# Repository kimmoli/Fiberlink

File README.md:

Fiberlink
=========

USB <-> 1000µm Fiber <-> RS-232 <-> RS-485

USB <-> RS232
SJ6, SJ7

USB <-> RS485
SJ10, SJ11, SJ15

USB <-> FIBER
SJ3, SJ5

RS232 <-> RS485
SJ12, SJ13, SJ14

RS232 <-> FIBER
SJ2, SJ4

FIBER <-> RS485
SJ8, SJ9, SJ14

SJ2 FIBER RX TO RS232
SJ3 FIBER RX TO USB
SJ4 RS232 RX TO FIBER
SJ5 USB RX TO FIBER
SJ6 USB RX TO RS232
SJ7 RS232 RX TO USB
SJ8 RS485 RX TO FIBER
SJ9 FIBER RX TO RS485
SJ10 RS485 RX TO USB
SJ11 USB RX TO RS485
SJ12 RS232 RX TO RS485
SJ13 RS485 RX TO RS232
SJ14 CARRIER SENSE TO RX485 TXEN
SJ15 USB TXEN TO RS485 TXEN

SJ17 FTDI POWER SELECT

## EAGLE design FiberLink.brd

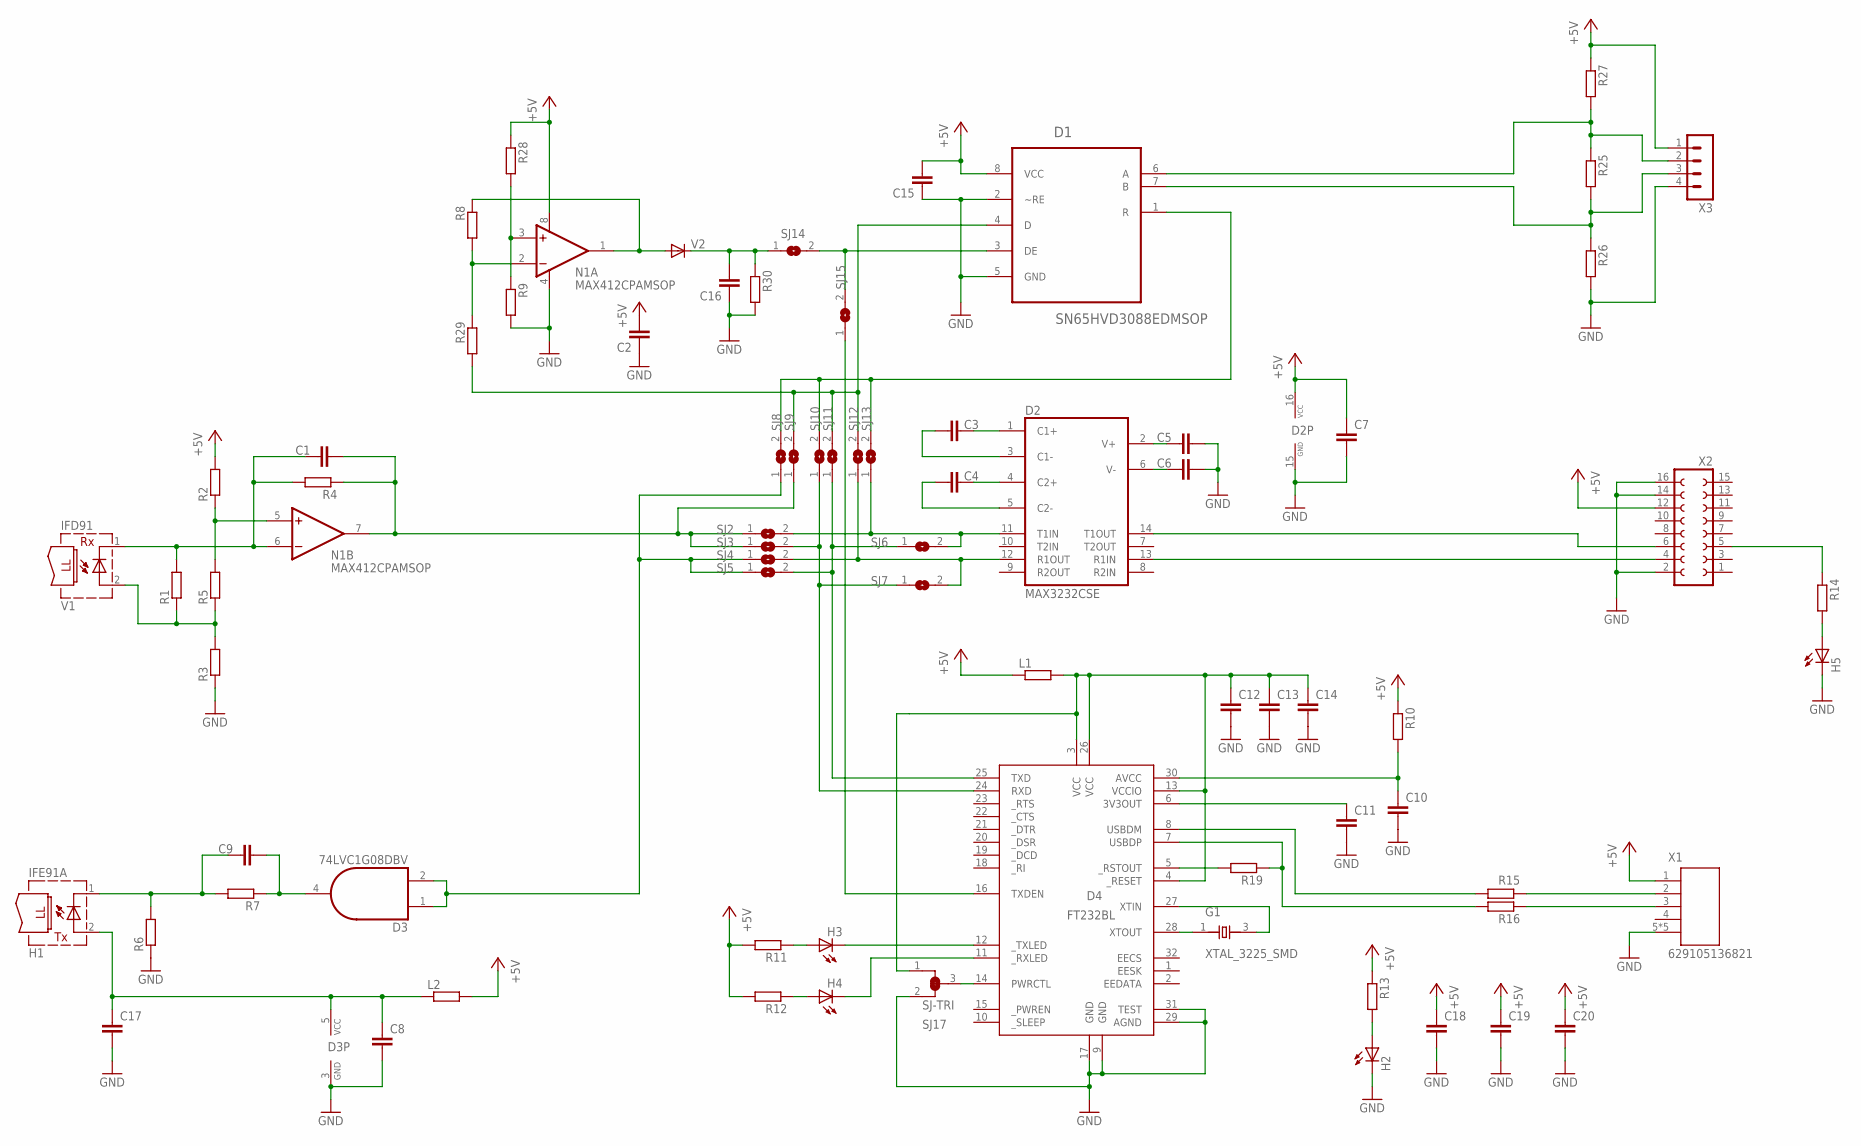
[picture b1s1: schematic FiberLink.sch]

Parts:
C1, C2, C3, C4, C5, C6, C7, C8, C9, C10, C11, C12, C13, C14, C15, C16, C17: C-EUC0402; C0402
C18, C19, C20: C-EUC0805; C0805
D1: SN65HVD3088EDMSOP; SOP65P490X110-8N
D2: MAX3232CSE; SO16
D3: 74LVC1G08DBV; SOT23-5
D4: FT232BL; LQFP32
G1: XTAL_3225_SMD; X_3225
H1: IFE91A; IFO-IFX
H2, H3, H4, H5: LEDCHIP-LED0603; CHIP-LED0603
L1, L2: R-EU_R0402; R0402_VISHAY
N1: MAX412CPAMSOP; SOP65P490X110-8N
R1, R2, R3, R4, R5, R8, R9, R10, R11, R12, R13, R14, R15, R16, R19, R28, R29, R30: R-EU_R0402; R0402_VISHAY
R6, R7, R25: R-EU_R1206; R1206
R26, R27: R-EU_R0603; R0603
SJ2, SJ3, SJ4, SJ5, SJ6, SJ7, SJ8, SJ9, SJ10, SJ11, SJ12, SJ13, SJ14, SJ15: SJ; SJ-SMALL
SJ17: SJ-TRI; SJ-SMALL-TRI
V1: IFD91; IFO-IFX
V2: DIODE-SOD323-R; SOD323-R
X1: 629105136821
X2: FE08-2
X3: MA04-1

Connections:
485_HIGH: D1.6 (A), R25.1, R27.2, X3.2
485_LOW: D1.7 (B), R25.2, R26.1, X3.3
+5V: C2.2, C7.1, C15.2, C18.1, C19.1, C20.1, D1.8 (VCC), D2.16 (VCC), L1.1, L2.2, N1.8 (V+), R2.2, R10.1, R11.2, R12.2, R13.1, R27.1, R28.1, X1.1, X2.12, X3.1
AVCC: C10.1, D4.30 (AVCC), R10.2
CARRIER_SENSE: C16.2, R30.1, SJ14.1, V2.C
FPGADONE: R14.1, X2.5
G1: D4.27 (XTIN), G1.3 (X2)
GND: C2.1, C5.2, C6.2, C7.2, C8.2, C10.2, C11.2, C12.2, C13.2, C14.2, C15.1, C16.1, C17.2, C18.2, C19.2, C20.2, D1.2 (~RE), D1.5 (GND), D2.15 (GND), D3.3 (GND), D4.9 (GND), D4.17 (GND), D4.29 (AGND), D4.31 (TEST), H2.C, H5.C, N1.4 (V-), R3.1, R6.1, R9.2, R26.2, R30.2, SJ17.2, X1.5, X1.Z1 (5), X1.Z2 (5), X1.Z3 (5), X1.Z4 (5), X2.2, X2.14, X2.16, X3.4
unnamed: C1.1, N1.6 (-IN), R1.2, R4.2, V1.1 (C)
unnamed: N1.1 (OUT), R8.1, V2.A
unnamed: R1.1, R3.2, R5.1, V1.2 (A)
unnamed: D4.12 (_TXLED), H3.C
unnamed: N1.5 (+IN), R2.1, R5.2
unnamed: C4.2, D2.5 (C2-)
unnamed: C4.1, D2.4 (C2+)
unnamed: C3.2, D2.3 (C1-)
unnamed: C3.1, D2.1 (C1+)
unnamed: C6.1, D2.6 (V-)
unnamed: C5.1, D2.2 (V+)
unnamed: D2.14 (T1OUT), X2.6
unnamed: D2.13 (R1IN), X2.4
unnamed: D4.11 (_RXLED), H4.C
unnamed: C9.1, H1.1 (C), R6.2, R7.2
unnamed: N1.3 (+IN), R9.1, R28.2
unnamed: C9.2, D3.4 (O), R7.1
unnamed: H3.A, R11.1
unnamed: R15.1, X1.2
unnamed: H4.A, R12.1
unnamed: D4.8 (USBDM), R15.2
unnamed: H2.A, R13.2
unnamed: D4.7 (USBDP), R16.2, R19.1
unnamed: R16.1, X1.3
unnamed: H5.A, R14.2
unnamed: D4.14 (PWRCTL), SJ17.3
unnamed: D4.5 (_RSTOUT), R19.2
unnamed: N1.2 (-IN), R8.2, R29.1
unnamed: D4.28 (XTOUT), G1.1 (X1)
RXD_232: D2.12 (R1OUT), SJ4.2, SJ7.2, SJ12.1
RXD_485: D1.1 (R), SJ8.2, SJ10.2, SJ13.2
RXD_FIBER: C1.2, N1.7 (OUT), R4.1, SJ2.1, SJ3.1, SJ9.1
RXD_USB: D4.24 (RXD), SJ3.2, SJ7.1, SJ10.1
TXD_232: D2.11 (T1IN), SJ2.2, SJ6.2, SJ13.1
TXD_485: D1.4 (D), R29.2, SJ9.2, SJ11.2, SJ12.2
TXD_FIBER: D3.1 (I0), D3.2 (I1), SJ4.1, SJ5.1, SJ8.1
TXD_USB: D4.25 (TXD), SJ5.2, SJ6.1, SJ11.1
TXEN_485: D1.3 (DE), SJ14.2, SJ15.2
TXEN_USB: D4.16 (TXDEN), SJ15.1
TX_VCC: C8.1, C17.1, D3.5 (VCC), H1.2 (A), L2.1
USB3V3: C11.1, D4.6 (3V3OUT)
USBVCC: C12.1, C13.1, C14.1, D4.3 (VCC), D4.4 (_RESET), D4.13 (VCCIO), D4.26 (VCC), L1.2, SJ17.1

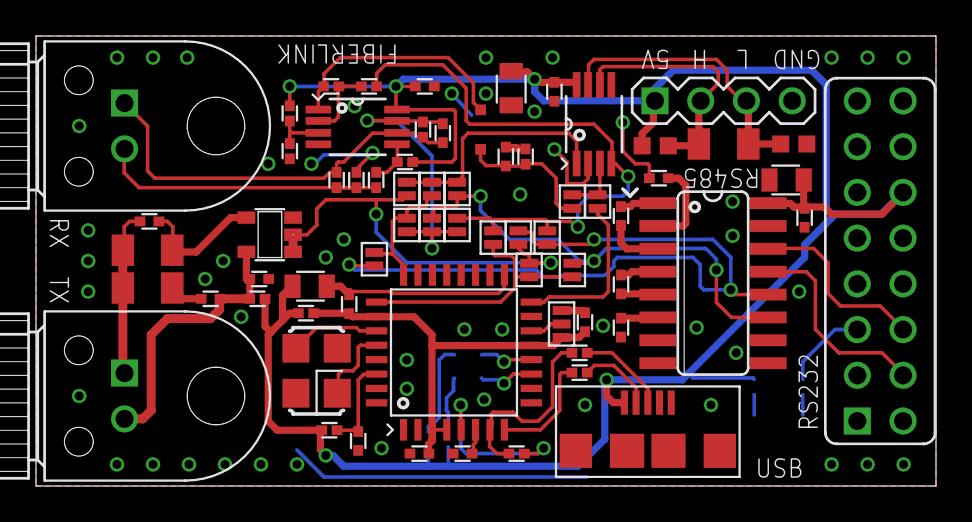
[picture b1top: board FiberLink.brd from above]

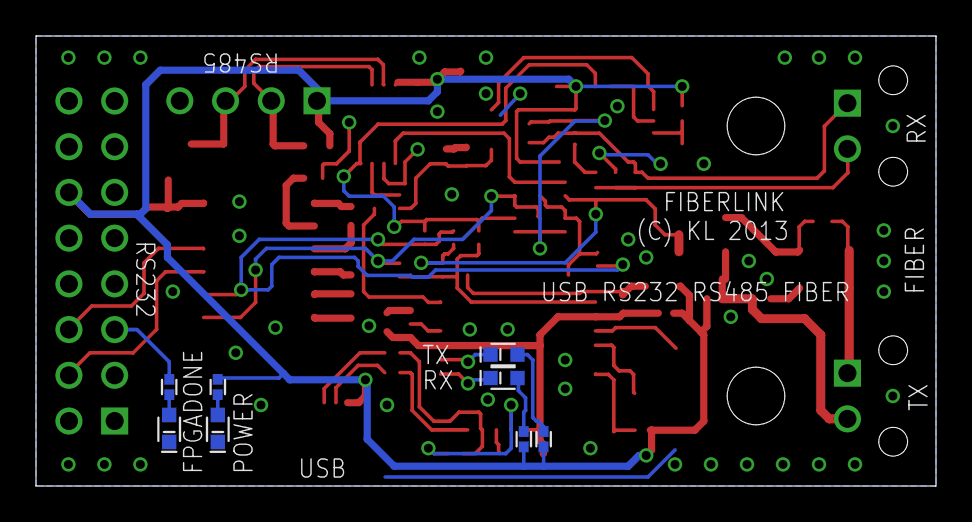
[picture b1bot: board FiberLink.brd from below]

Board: 2 copper layers, 50.0 x 25.0 mm, 77 parts (8 on the bottom side), 50 nets.

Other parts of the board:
DRILEGEND: DRILEGEND

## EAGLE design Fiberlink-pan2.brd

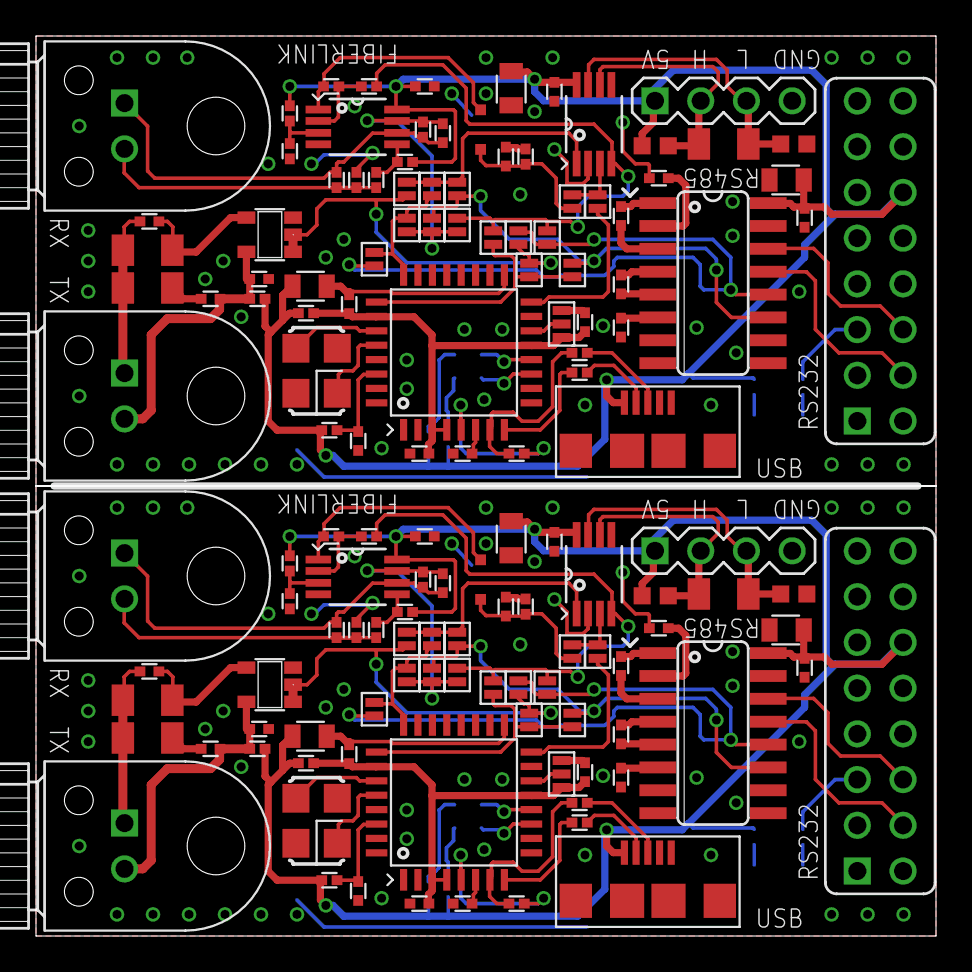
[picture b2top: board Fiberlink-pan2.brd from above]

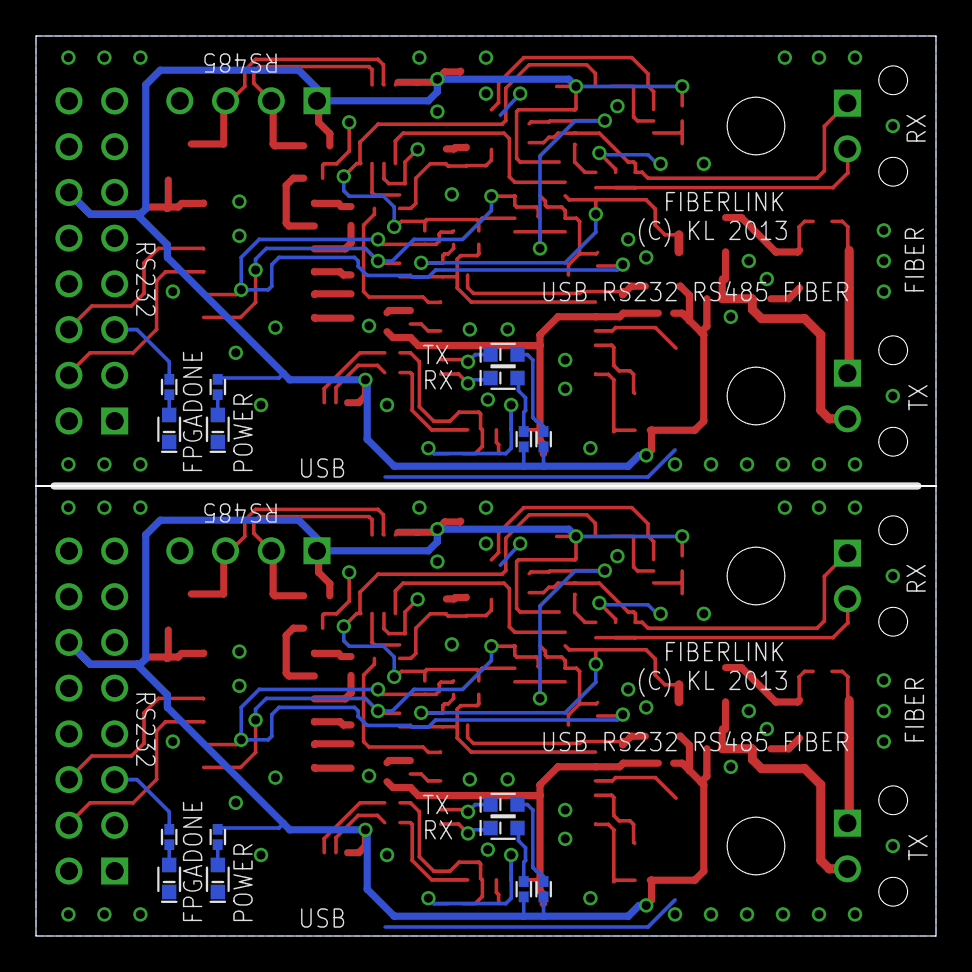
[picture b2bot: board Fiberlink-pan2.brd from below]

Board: 2 copper layers, 50.0 x 50.0 mm, 153 parts (16 on the bottom side), 100 nets.

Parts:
C1, C2, C3, C4, C5, C6, C7, C8, C9, C10, C11, C12, C13, C14, C15, C16, C17, C21, C22, C23, C24, C25, C26, C27, C28, C29, C30, C31, C32, C33, C34, C35, C36, C37: C0402
C18, C19, C20, C38, C39, C40: C0805
D1, D8: SN65HVD3088EDMSOP; SOP65P490X110-8N
D2, D5: MAX3232CSE; SO16
D3, D6: 74LVC1G08DBV; SOT23-5
D4, D7: FT232BL; LQFP32
DRILEGEND: DRILEGEND
G1, G2: XTAL_3225_SMD; X_3225
H1, H6: IFE91A; IFO-IFX
H2, H3, H4, H5, H7, H8, H9, H10: CHIP-LED0603
L1, L2, L3, L4: R0402_VISHAY
N1, N2: MAX412CPAMSOP; SOP65P490X110-8N
R1, R2, R3, R4, R5, R8, R9, R10, R11, R12, R13, R14, R15, R16, R17, R18, R19, R20, R21, R22, R28, R29, R30, R31, R32, R33, R34, R35, R36, R40, R41, R42, R43, R44, R45, R46: R0402_VISHAY
R6, R7, R23, R24, R25, R37: R1206
R26, R27, R38, R39: R0603
SJ1, SJ2, SJ3, SJ4, SJ5, SJ6, SJ7, SJ8, SJ9, SJ10, SJ11, SJ12, SJ13, SJ14, SJ15, SJ16, SJ18, SJ19, SJ20, SJ21, SJ22, SJ23, SJ24, SJ25, SJ26, SJ27, SJ28, SJ29: SJ-SMALL
SJ17, SJ30: SJ-TRI; SJ-SMALL-TRI
V1, V4: IFD91; IFO-IFX
V2, V3: SOD323-R
X1, X5: 629105136821
X2, X4: FE08-2
X3, X6: MA04-1

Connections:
485_HIGH: D1.6, R25.1, R27.2, X3.2
485_HIGH1: D8.6, R37.1, R39.2, X6.2
485_LOW: D1.7, R25.2, R26.1, X3.3
485_LOW1: D8.7, R37.2, R38.1, X6.3
+5V: C2.2, C7.1, C15.2, C18.1, C19.1, C20.1, D1.8, D2.16, L1.1, L2.2, N1.8, R2.2, R10.1, R11.2, R12.2, R13.1, R27.1, R28.1, X1.1, X2.12, X3.1
+5V1: C22.2, C27.1, C35.2, C38.1, C39.1, C40.1, D5.16, D8.8, L3.1, L4.2, N2.8, R18.2, R33.1, R39.1, R40.1, R43.2, R44.2, R45.1, X4.12, X5.1, X6.1
AVCC: C10.1, D4.30, R10.2
AVCC1: C30.1, D7.30, R33.2
CARRIER_SENSE: C16.2, R30.1, SJ14.1, V2.C
CARRIER_SENSE1: C36.2, R42.1, SJ28.1, V3.C
FPGADONE: R14.1, X2.5
FPGADONE1: R46.1, X4.5
G1: D4.27, G1.3
G2: D7.27, G2.3
GND: C2.1, C5.2, C6.2, C7.2, C8.2, C10.2, C11.2, C12.2, C13.2, C14.2, C15.1, C16.1, C17.2, C18.2, C19.2, C20.2, D1.2, D1.5, D2.15, D3.3, D4.9, D4.17, D4.29, D4.31, H2.C, H5.C, N1.4, R3.1, R6.1, R9.2, R26.2, R30.2, SJ17.2, X1.5, X1.Z1, X1.Z2, X1.Z3, X1.Z4, X2.2, X2.14, X2.16, X3.4
GND1: C22.1, C25.2, C26.2, C27.2, C28.2, C30.2, C31.2, C32.2, C33.2, C34.2, C35.1, C36.1, C37.2, C38.2, C39.2, C40.2, D5.15, D6.3, D7.9, D7.17, D7.29, D7.31, D8.2, D8.5, H9.C, H10.C, N2.4, R20.1, R23.1, R32.2, R38.2, R42.2, SJ30.2, X4.2, X4.14, X4.16, X5.5, X5.Z1, X5.Z2, X5.Z3, X5.Z4, X6.4
unnamed: C1.1, N1.6, R1.2, R4.2, V1.1
unnamed: N1.1, R8.1, V2.A
unnamed: R1.1, R3.2, R5.1, V1.2
unnamed: D4.12, H3.C
unnamed: N1.5, R2.1, R5.2
unnamed: C4.2, D2.5
unnamed: C4.1, D2.4
unnamed: C3.2, D2.3
unnamed: C3.1, D2.1
unnamed: C6.1, D2.6
unnamed: C5.1, D2.2
unnamed: D2.14, X2.6
unnamed: D2.13, X2.4
unnamed: D4.11, H4.C
unnamed: C9.1, H1.1, R6.2, R7.2
unnamed: N1.3, R9.1, R28.2
unnamed: C9.2, D3.4, R7.1
unnamed: H3.A, R11.1
unnamed: R15.1, X1.2
unnamed: H4.A, R12.1
unnamed: D4.8, R15.2
unnamed: H2.A, R13.2
unnamed: D4.7, R16.2, R19.1
unnamed: R16.1, X1.3
unnamed: H5.A, R14.2
unnamed: D4.14, SJ17.3
unnamed: C21.1, N2.6, R17.2, R21.2, V4.1
unnamed: R17.1, R20.2, R22.1, V4.2
unnamed: D4.5, R19.2
unnamed: N2.5, R18.1, R22.2
unnamed: C24.2, D5.5
unnamed: N1.2, R8.2, R29.1
unnamed: D4.28, G1.1
unnamed: C24.1, D5.4
unnamed: C23.2, D5.3
unnamed: C23.1, D5.1
unnamed: C26.1, D5.6
unnamed: C25.1, D5.2
unnamed: D5.14, X4.6
unnamed: C29.1, H6.1, R23.2, R24.2
unnamed: C29.2, D6.4, R24.1
unnamed: N2.1, R31.1, V3.A
unnamed: N2.3, R32.1, R40.2
unnamed: R34.1, X5.2
unnamed: D7.8, R34.2
unnamed: D7.7, R35.2, R36.1
unnamed: R35.1, X5.3
unnamed: D7.5, R36.2
unnamed: D7.28, G2.1
unnamed: D5.13, X4.4
unnamed: N2.2, R31.2, R41.1
unnamed: D7.12, H7.C
unnamed: D7.11, H8.C
unnamed: H7.A, R43.1
unnamed: H8.A, R44.1
unnamed: H9.A, R45.2
unnamed: H10.A, R46.2
unnamed: D7.14, SJ30.3
RXD_1: D5.12, SJ18.2, SJ21.2, SJ26.1
RXD_2: D8.1, SJ22.2, SJ24.2, SJ27.2
RXD_232: D2.12, SJ4.2, SJ7.2, SJ12.1
RXD_485: D1.1, SJ8.2, SJ10.2, SJ13.2
RXD_FIBER: C1.2, N1.7, R4.1, SJ2.1, SJ3.1, SJ9.1
RXD_FIBER1: C21.2, N2.7, R21.1, SJ1.1, SJ16.1, SJ23.1
RXD_USB: D4.24, SJ3.2, SJ7.1, SJ10.1
RXD_USB1: D7.24, SJ16.2, SJ21.1, SJ24.1
TXD_1: D5.11, SJ1.2, SJ20.2, SJ27.1
TXD_2: D8.4, R41.2, SJ23.2, SJ25.2, SJ26.2
TXD_232: D2.11, SJ2.2, SJ6.2, SJ13.1
TXD_485: D1.4, R29.2, SJ9.2, SJ11.2, SJ12.2
TXD_FIBER: D3.1, D3.2, SJ4.1, SJ5.1, SJ8.1
TXD_FIBER1: D6.1, D6.2, SJ18.1, SJ19.1, SJ22.1
TXD_USB: D4.25, SJ5.2, SJ6.1, SJ11.1
TXD_USB1: D7.25, SJ19.2, SJ20.1, SJ25.1
TXEN_1: D8.3, SJ28.2, SJ29.2
TXEN_485: D1.3, SJ14.2, SJ15.2
TXEN_USB: D4.16, SJ15.1
TXEN_USB1: D7.16, SJ29.1
TX_VCC: C8.1, C17.1, D3.5, H1.2, L2.1
TX_VCC1: C28.1, C37.1, D6.5, H6.2, L4.1
USB3V1: C31.1, D7.6
USB3V3: C11.1, D4.6
USBVCC: C12.1, C13.1, C14.1, D4.3, D4.4, D4.13, D4.26, L1.2, SJ17.1
USBVCC1: C32.1, C33.1, C34.1, D7.3, D7.4, D7.13, D7.26, L3.2, SJ30.1

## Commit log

2013-06-15 changed passive packages
2013-06-15 first completely routed
2013-06-15 Added some leds
2013-06-15 ITEAD cam file added
2013-06-15 ITEAD design rule check added
2013-06-15 New filenames
2013-06-15 Panelisation added. Corrected drill sizes
2013-06-15 PDF Schematic added
2013-06-15 PDF Layout added
2013-06-15 Configuration documentation added
